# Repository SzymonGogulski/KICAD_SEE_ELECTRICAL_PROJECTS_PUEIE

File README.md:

**English version at the bottom.**
# Projektowanie Układów Elektrycznych i Elektronicznych
To repozytorium zawiera dokumentację oraz projekty wykonane w ramach przedmiotu Projektowanie Układów Elektrycznych i Elektronicznych na 7 semestrze kierunku Automatyka i Robotyka na Politechnice Poznańskiej. Autorami projektów są Marcin Gałąska i Szymon Gogulski.
### Główne cele projektów
1. <b> Opracowanie projektu układu elektrycznego sterującego mikroklimatem terrarium dla kameleona. </b>
    - Układ steruje parametrami mikroklimatu terrarium.
    - Automatyczna regulacja temperatury poprzez jedną dzienną oraz jedną nocną lampę grzewczą. 
    - Automatyczna regulacja oświetlenia poprzez świetlówkę UVB.
    - Automatyczna regulacja wilgotności poprzez zanurzony w zbiorniku wodnym fogger.
    - Pomiar temperatury i wilgotności powietrza poprzez czujniki z przetwornikami.
    - Informowanie o stanie mikroklimatu poprzez panel HMI.
2. <b> Opracowanie projektu układu elektronicznego oraz projektu płytki PCB dalmierza laserowego. </b>
    - Urządzenie wykonuje pomiar odległości czujnikiem laserowym i ultradźwiękowym.
    - Urządzenie jest zasilane z ogniwa LI-ION lub z baterii 9V.
    - Urządzenie posiada 6 przycisków.
    - Urządzenie posiada wyświetlacz LCD 4x20.
    - Urządzenie wykonuje pomiar naładowania akumulatora/ baterii.
    - Urządzenie obsługuje transmisję bluetooth.
***
# Dalmierz
- Projekt opiera się o dokumentację mikroprocesora RP2040.
- Projekt został wykonany w programi KiCad7.0.

### Schemat ideowy projektu

### Schemat elektronicznych

Schemat lepiej widoczny w jasnym motywie GitHub.

### Płytka PCB

### Płytka PCB 3D

### Zasilanie 
1. W celu zasilenia układu wykorzystaliśmy ogniwo li-ion 18650.
2. Układ składa się z dwóch przetwornic: BUCK-BOOST RT6150B-33GQW zapewniającej napięcie 3.3V oraz BOOST LM2775DSG zapewniającej napięcie 5V.
3. Przed wybraniem przetwornic przeprowadziliśmy rachunek poboru prądu przy założeniu najwyższego obciążenia.
4. W ramach monitorowania stanu naładowania ogniwa zastosowaliśmy moduł LC709203. Moduł ten umożliwia bieżące przekazywanie informacji o stanie ogniwa poprzez interface I2C do mikrokontrolera.
5. Wejścia układu zostały zabezpieczone diodami Schottkiego na wypadek odwrotnego zamontowania ogniwa w gnieździe.

### Czujniki
Czujniki odległości będą podłączane do układu poprzez konektory I2C

### Bluetooth
W ramach możliwości zapisu pomiarów na urządzeniu zewnętrznym dodaliśmy moduł komunikacji bluetooth.

### Macierz przycisków / Wyświetlacz I2C LCD
1. Jako interface użytkownika zastosowaliśmy macierz  sześciu przycisków oraz wyświetlacz I2C.
2. Na płytce zamontowaliśmy osobny konektory I2C umożliwiający podłączenie wyświetlacza.
3. W celu uniknięcia drgań styków lepszym rozwiązanie byłoby zastosowanie dodatkowych filtrów RC pomiędzy przyciskami oraz mikrokontrolerem.

### RP2040, pamięć Flash i oscylator
Sercem układu jest mikrokontroler RP2040, sugerowany schemat mikrokontrolera, pamięci flash i oscylatora kwarcowego został wykorzystany z ogólnodostępnej dokumentacji.
### Programowanie
Wejście USB micro B zostało dodane, aby umożliwić bieżący rozwój oprogramowania.

***

# Terarrium
- Projekt opiera się o sterownik PLC DC/DC/RELAY firmy Siemens serii S7-1200 model 6ES7212-1HE40-0XB0.
- Projekt został wykonany w programie SEE Electrical V8R4.

### Zasilanie
1. Głównym źródłem zasilania układu jest standardowa jednofazowa linia AC 230V 50Hz z przewodem uziemiającym.
2. Obwód zasilania zawiera wyłącznik nadprądowy MCN110E oraz wkładkę bezpiecznikową 1115282107T dla fazy, wraz z wyłącznikiem różnicowoprądowym CFI6-25/2/003 dla żyły fazy i odniesienia.
3. Rozgałęzienia linii głównej przechodzą przez styki stycznika iCT50-25-20-230, włączonego w obwód włącznika i wyłącznika głównego.
4. Podłączonym do głównej linii zasilania jest zasilacz AST-PWR-7524 firmy Astor, konwertujący otrzymywane 230 AC na 24 DC, służące do zasilania szeregu komponentów w układzie.

### Czujniki
Pomiar temperatury wykonywany jest poprzez trójprzewodowy czujnik Pt100 sparowany z przetwornikiem AR580. Pomiar wilgotności powietrza realizowany jest poprzez układ czujnika z przetwornikiem AR250. Oba czujniki przekazują swój sygnał wejściowy z zakresu 0...10V DC na wejścia analogowe sterownika PLC. Oba czujniki zasilane są z linii 24V DC.

### Elementy wykonawcze
Grzanie nocne wykonuje lampa grzewcza Exo Terra Ceramic Heat Emitter 50W PT2044, wkręcona w żaroodporny klosz PT2060. Grzanie nocne wykonuje lampa grzewcza Exo Terra Night Heat Lamp 25W PT2122, wkręcona w żaroodporny klosz PT2060. Oświetlenie terrarium zapewniane jest poprzez świetlówkę Exo Terra Reptile UVB Nano 9W PT2366, wkręconą w klosz PT2364. Elementem nawilżającym powietrze wewnątrz terrarium jest membranowy fogger Exo Terra Fogger Ultrasonic Fog Generator PT2080. Elementy te zasilane są z sieci 230 AC, jednak w swoich obwodach posiadają styki styczników pomocniczych CA3SK11BD, których cewki podłączone są do wyjść cyfrowych sterownika PLC, celem kontroli zasilania każdego z elementów wykonawczych.

### Wizualizacja stanu mikroklimatu
Elementem informującym użytkownika o parametrach mikroklimatu terrarium jest panel HMI Simatic KTP400 6AV2123-2DB03-0AX0 firmy Siemens, połączony ze sterownikiem PLC poprzez złącze Ethernet.

### Szafa rozdzielcza

***

# Design of Electrical and Electronic Systems
This repository contains documentation and projects made as part of the course Design of Electrical and Electronic Systems in the 7th semester of the Automation and Robotics major at the Poznań University of Technology. The authors of the projects are Marcin Gałąska and Szymon Gogulski.
### Main project goals
1. <b> Development of an electrical system controlling the microclimate of a chameleon terrarium. </b>
    - The system controls the parameters of the terrarium microclimate.
    - Automatic temperature control using one daytime and one nighttime heating lamp.
    - Automatic lighting control using a UVB fluorescent lamp.
    - Automatic humidity control using a fogger immersed in the water tank.
    - Measurement of air temperature and humidity using sensors with transducers.
    - Information about the microclimate status using the HMI panel.
2. <b> Development of an electronic circuit and a PCB design for a laser rangefinder. </b>
    - The device measures distance with a laser and ultrasonic sensor.
    - The device is powered by a LI-ION cell or a 9V battery.
    - The device has 6 buttons.
    - The device has a 4x20 LCD display.
    - The device measures the battery charge.
    - The device supports Bluetooth transmission.
***
# Rangefinder
- The project is based on the RP2040 microprocessor documentation.
- The project was made in KiCad7.0.

### Project flowchart

### Electronic diagram

Diagram more visible in GitHub's light theme.

### PCB board

### PCB board 3D view

### Power supply
1. To power the system, we used a 18650 Li-ion cell.
2. The system consists of two converters: BUCK-BOOST RT6150B-33GQW providing a voltage of 3.3V and BOOST LM2775DSG providing a voltage of 5V.
3. Before selecting the converters, we calculated the current consumption assuming the highest load.
4. TO monitor the cell charge status, we used the LC709203 module. This module allows the transmission of information about the cell status via the I2C interface to the microcontroller.
5. The inputs of the system were protected with Schottky diodes in case the cell is mounted in the socket the other way around.

### Sensors
Distance sensors will be connected to the system via I2C connectors

### Bluetooth
In order to enable the recording of measurements on an external device, we have added a Bluetooth communication module.

### Button matrix / I2C LCD display
1. We have used a matrix of six buttons and an I2C display as the user interface.

2. We have mounted separate I2C connectors on the board to connect the display.

3. In order to avoid contact vibrations, a better solution would be to use additional RC filters between the buttons and the microcontroller.

### RP2040, Flash memory and oscillator
The heart of the system is the RP2040 microcontroller, the suggested diagram of the microcontroller, flash memory and quartz oscillator was used from publicly available documentation.

### Programming
The USB micro B inputs were left to enable ongoing software development.

***

# Terarrium
- The project is based on the Siemens S7-1200 series PLC DC/DC/RELAY model 6ES7212-1HE40-0XB0.
- The project was made in the SEE Electrical V8R4 program.

### Power supply
1. The main power supply for the system is a standard single-phase AC 230V 50Hz line with a ground wire.

2. The power supply circuit includes an MCN110E circuit breaker and a 1115282107T fuse insert for the phase, along with a CFI6-25/2/003 differential circuit breaker for the phase and reference wires.

3. The main line branches pass through the contacts of the iCT50-25-20-230 contactor, included in the main switch and switch circuit.
4. Connected to the main power line is the Astor AST-PWR-7524 power supply, converting the received 230 AC to 24 DC, used to power a number of components in the system.

### Sensors
Temperature measurement is performed by a three-wire Pt100 sensor paired with an AR580 transducer. Air humidity measurement is performed by a sensor system with an AR250 transducer. Both sensors transmit their input signal from the 0...10V DC range to the analog inputs of the PLC controller. Both sensors are powered from the 24V DC line.

### Actuators
Night heating is performed by the Exo Terra Ceramic Heat Emitter 50W PT2044 heating lamp, screwed into a heat-resistant PT2060 lampshade. Night heating is performed by the Exo Terra Night Heat Lamp 25W PT2122 heating lamp, screwed into a heat-resistant PT2060 lampshade. Terrarium lighting is provided by an Exo Terra Reptile UVB Nano 9W PT2366 fluorescent lamp, screwed into a PT2364 lampshade. The element that humidifies the air inside the terrarium is the Exo Terra Fogger Ultrasonic Fog Generator PT2080 membrane fogger. These elements are powered from the 230 AC network, but in their circuits they have contacts of auxiliary contactors CA3SK11BD, the coils of which are connected to the digital outputs of the PLC controller, in order to control the power supply of each of the executive elements.

### Visualization of the microclimate state
The element informing the user about the parameters of the terrarium microclimate is the HMI panel Simatic KTP400 6AV2123-2DB03-0AX0 by Siemens, connected to the PLC controller via an Ethernet port.

### Switchboard

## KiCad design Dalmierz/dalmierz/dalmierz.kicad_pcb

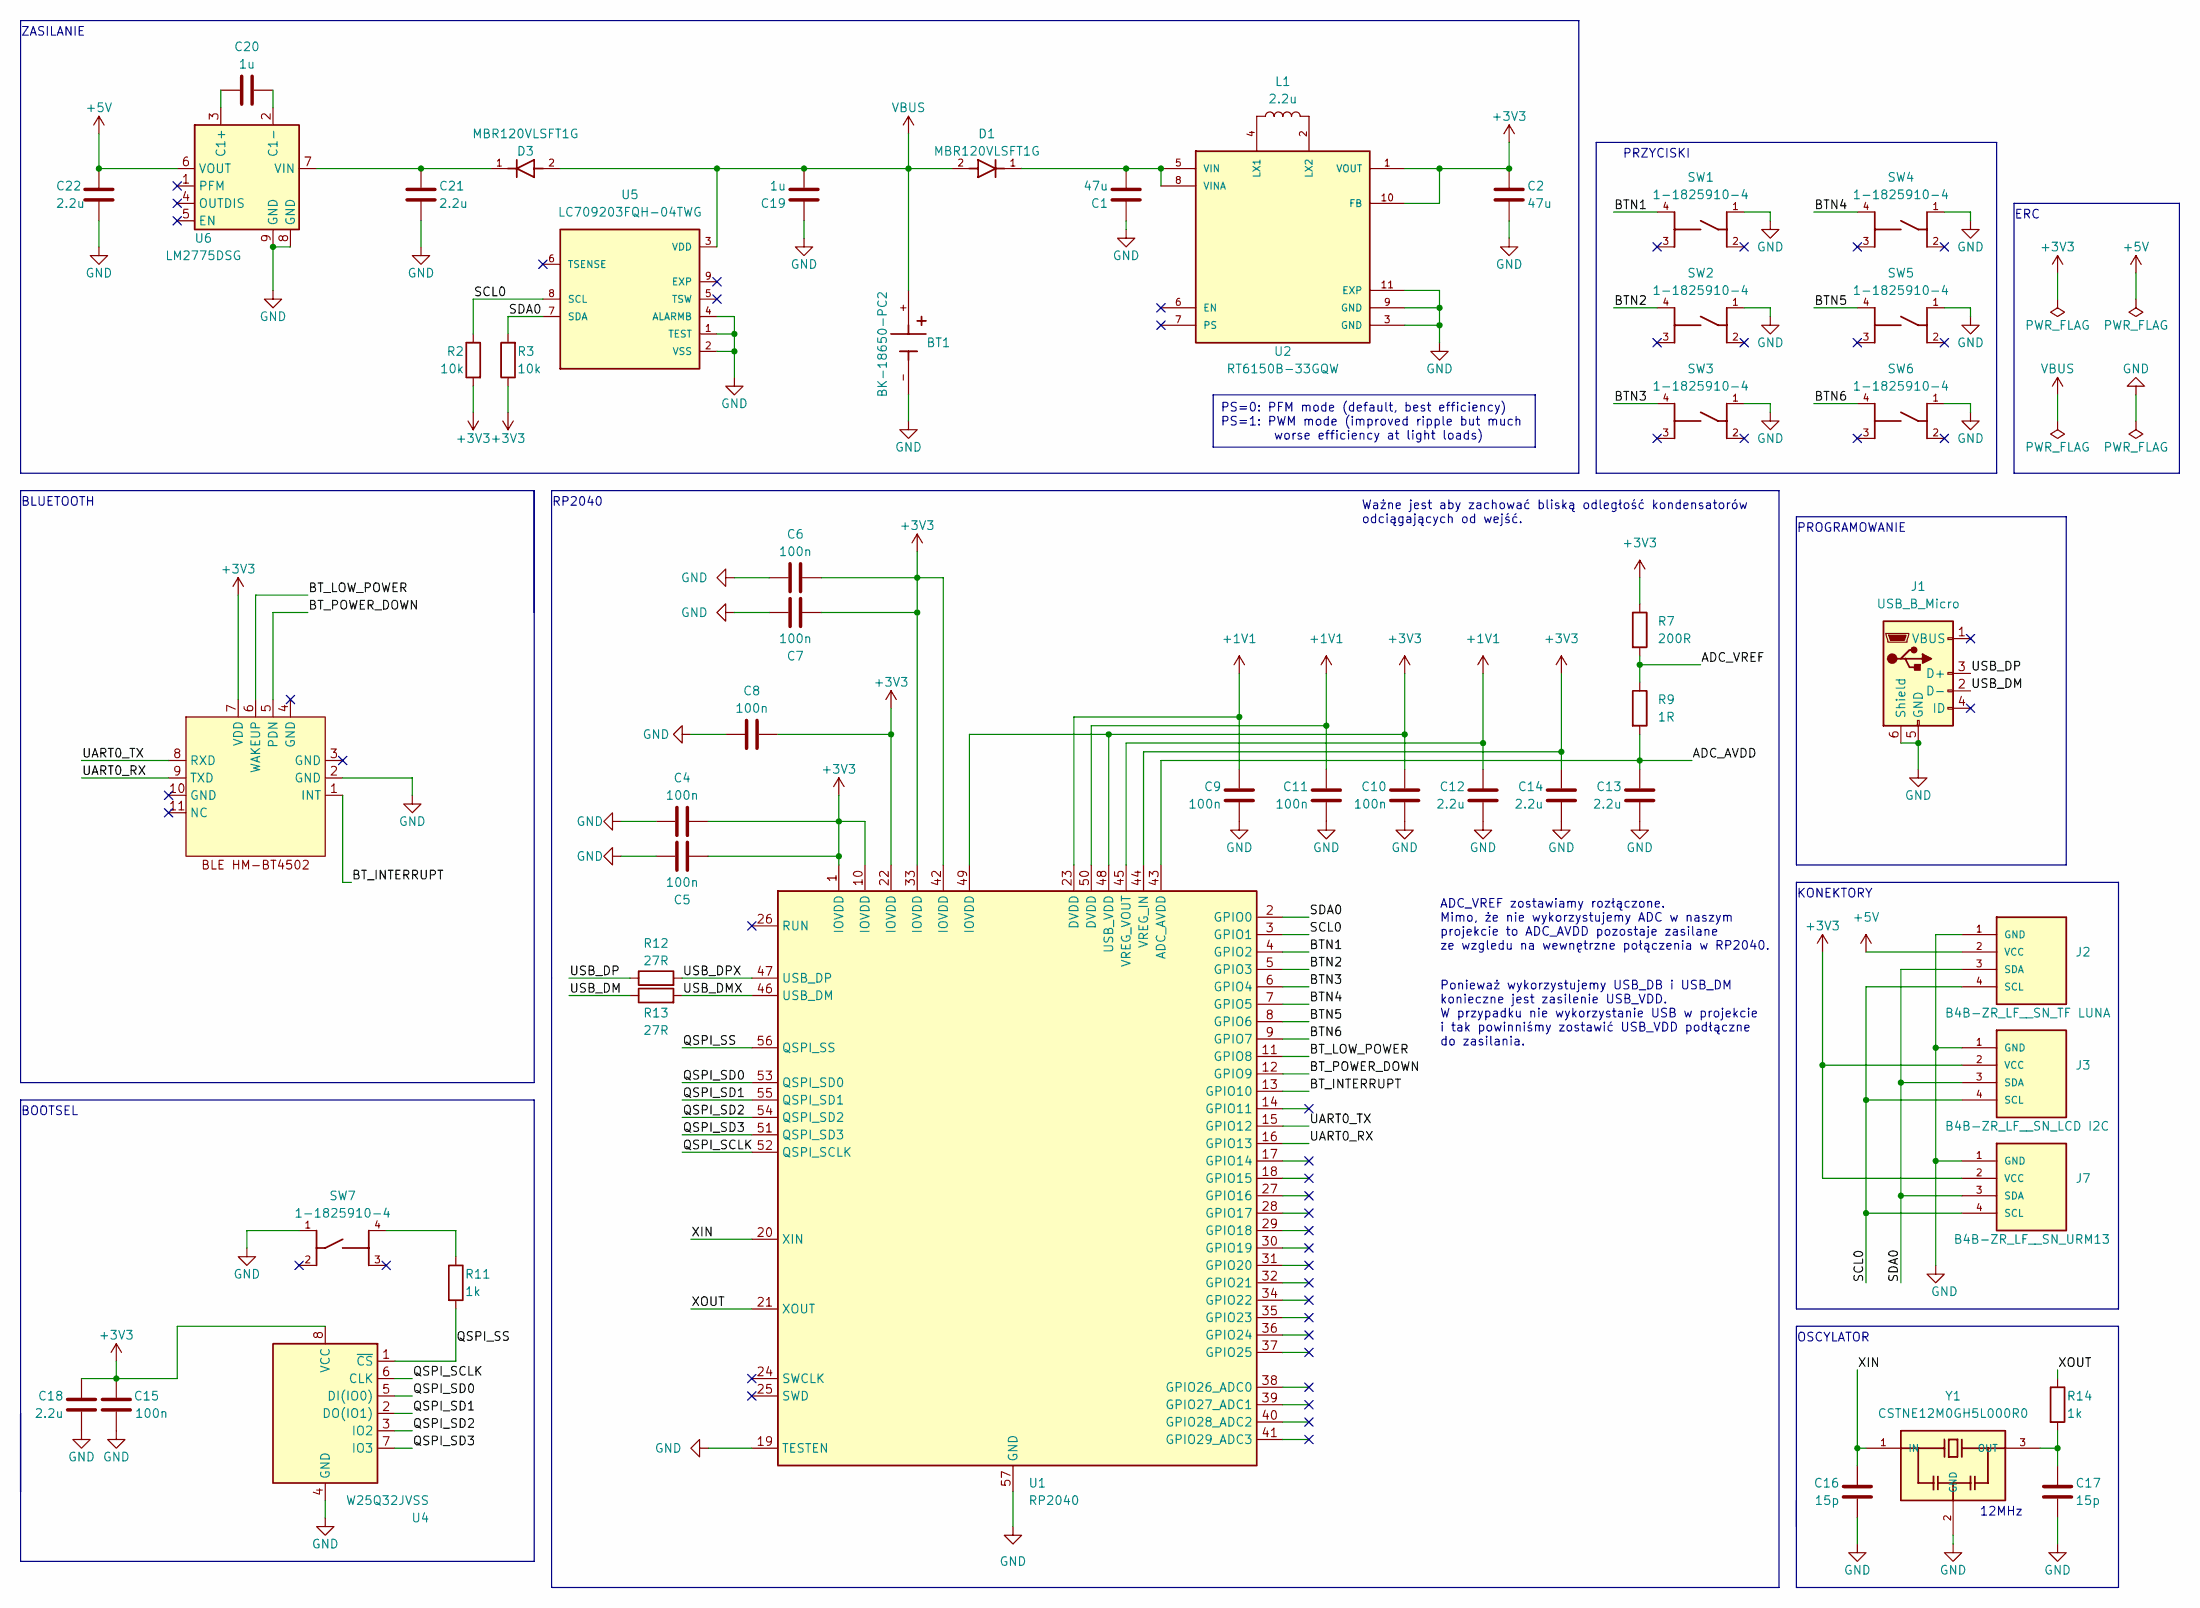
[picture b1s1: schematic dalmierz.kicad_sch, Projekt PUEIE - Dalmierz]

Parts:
B1: BLE_HM-BT5402
BT1: BK-18650-PC2; BAT_BK-18650-PC2; PARTREV F
C1, C2: 47u; C_0603_1608Metric
C4, C5, C6, C7, C8, C9, C10, C11, C15: 100n; C_0603_1608Metric
C12, C13, C14, C18, C21, C22: 2.2u; C_0603_1608Metric
C16, C17: 15p; C_0603_1608Metric
C19, C20: 1u; C_0603_1608Metric
D1, D3: MBR120VLSFT1G; DIOM3616X98N; PARTREV 5/10/2013
J1: USB_B_Micro; USB_Micro-B_Amphenol_10103594-0001LF_Horizontal
J2: B4B-ZR_LF__SN_TF LUNA; JST_B4B-ZR_LF__SN_
J3: B4B-ZR_LF__SN_LCD I2C; JST_B4B-ZR_LF__SN_
J7: B4B-ZR_LF__SN_URM13; JST_B4B-ZR_LF__SN_
L1: 2.2u; L_0603_1608Metric
R2, R3: 10k; R_0603_1608Metric
R7: 200R; R_0603_1608Metric
R9: 1R; R_0603_1608Metric
R11, R14: 1k; R_0603_1608Metric
R12, R13: 27R; R_0603_1608Metric
SW1, SW2, SW3, SW4, SW5, SW6, SW7: 1-1825910-4; TE_1-1825910-4; PARTREV C10
U1: RP2040; QFN-56-1EP_7x7mm_P0.4mm_EP3.2x3.2mm
U2: RT6150B-33GQW; SON50P250X250X80-11N; PARTREV July 2018
U4: W25Q32JVSS; SOIC-8_5.23x5.23mm_P1.27mm
U5: LC709203FQH-04TWG; DFN300X400X80-8N
U6: LM2775DSG; WSON-8-1EP_2x2mm_P0.5mm_EP0.9x1.6mm
Y1: CSTNE12M0GH5L000R0; OSC_CSTNE12M0GH5L000R0; PARTREV JGC42-8858A

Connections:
+1V1: C9.1, C11.1, C12.1, U1.23 (DVDD), U1.45 (VREG_VOUT), U1.50 (DVDD)
+3V3: B1.7 (VDD), C2.1, C4.2, C5.2, C6.2, C7.2, C8.2, C10.1, C14.1, C15.1, C18.1, J3.2 (VCC), J7.2 (VCC), R2.2, R3.1, R7.1, U1.1 (IOVDD), U1.10 (IOVDD), U1.22 (IOVDD), U1.33 (IOVDD), U1.42 (IOVDD), U1.44 (VREG_IN), U1.48 (USB_VDD), U1.49 (IOVDD), U2.1 (VOUT), U2.10 (FB), U4.8 (VCC); also elsewhere on the board
+5V: C22.1, J2.2 (VCC), U6.6 (VOUT)
/ADC_AVDD: C13.1, R9.2, U1.43 (ADC_AVDD)
/ADC_VREF: R7.2, R9.1
/BTN1: SW1.4, U1.4 (GPIO2)
/BTN2: SW2.4, U1.5 (GPIO3)
/BTN3: SW3.4, U1.6 (GPIO4)
/BTN4: SW4.4, U1.7 (GPIO5)
/BTN5: SW5.4, U1.8 (GPIO6)
/BTN6: SW6.4, U1.9 (GPIO7)
/BT_INTERRUPT: B1.1 (INT), U1.13 (GPIO10)
/BT_LOW_POWER: B1.6 (WAKEUP), U1.11 (GPIO8)
/BT_POWER_DOWN: B1.5 (PDN), U1.12 (GPIO9)
/QSPI_SCLK: U1.52 (QSPI_SCLK), U4.6 (CLK)
/QSPI_SD0: U1.53 (QSPI_SD0), U4.5 (DI(IO0))
/QSPI_SD1: U1.55 (QSPI_SD1), U4.2 (DO(IO1))
/QSPI_SD2: U1.54 (QSPI_SD2), U4.3 (IO2)
/QSPI_SD3: U1.51 (QSPI_SD3), U4.7 (IO3)
/QSPI_SS: R11.2, U1.56 (QSPI_SS), U4.1 (~CS)
/SCL0: J2.4 (SCL), J3.4 (SCL), J7.4 (SCL), R2.1, U1.3 (GPIO1), U5.8 (SCL)
/SDA0: J2.3 (SDA), J3.3 (SDA), J7.3 (SDA), R3.2, U1.2 (GPIO0), U5.7 (SDA)
/UART0_RX: B1.9 (TXD), U1.16 (GPIO13)
/UART0_TX: B1.8 (RXD), U1.15 (GPIO12)
/USB_DM: J1.2 (D-), R13.1
/USB_DMX: R13.2, U1.46 (USB_DM)
/USB_DP: J1.3 (D+), R12.1
/USB_DPX: R12.2, U1.47 (USB_DP)
/XIN: C16.1, U1.20 (XIN), Y1.1 (IN)
/XOUT: R14.1, U1.21 (XOUT)
GND: B1.2 (GND), B1.3 (GND), B1.4 (GND), B1.10 (GND), B1.11 (NC), BT1.-, C1.1, C2.2, C4.1, C5.1, C6.1, C7.1, C8.1, C9.2, C10.2, C11.2, C12.2, C13.2, C14.2, C15.2, C16.2, C17.2, C18.2, C19.1, C21.1, C22.2, J1.5 (GND), J1.6 (Shield), J2.1 (GND), J3.1 (GND), J7.1 (GND), SW1.1, SW2.1, SW3.1, SW4.1, SW5.1, SW6.1, SW7.1, U1.19 (TESTEN), U1.57 (GND), U2.3 (GND), U2.9 (GND), U2.11 (EXP), U4.4 (GND), U5.1 (TEST), U5.2 (VSS), U5.4 (ALARMB), U6.8 (GND), U6.9 (GND), Y1.2 (GND); also elsewhere on the board
unnamed: R11.1, SW7.4
unnamed: L1.1, U2.4 (LX1)
unnamed: L1.2, U2.2 (LX2)
unnamed: C1.2, D1.1, U2.5 (VIN), U2.8 (VINA)
unnamed: C20.2, U6.3 (C1+)
unnamed: C20.1, U6.2 (C1-)
unnamed: C21.2, D3.1, U6.7 (VIN)
unnamed: C17.1, R14.2, Y1.3 (OUT)
VBUS: BT1.+, C19.2, D1.2, D3.2, U5.3 (VDD)

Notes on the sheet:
PS=0: PFM mode (default, best efficiency) PS=1: PWM mode (improved ripple but much worse efficiency at light loads)
OSCYLATOR
PROGRAMOWANIE
BLUETOOTH
PRZYCISKI
ADC_VREF zostawiamy rozłączone. Mimo, że nie wykorzystujemy ADC w naszym projekcie to ADC_AVDD pozostaje zasilane ze wzgledu na wewnętrzne połączenia w RP2040.
ERC
Ponieważ wykorzystujemy USB_DB i USB_DM konieczne jest zasilenie USB_VDD. W przypadku nie wykorzystanie USB w projekcie i tak powinniśmy zostawić USB_VDD podłączne do zasilania.
KONEKTORY
RP2040
12MHz
ZASILANIE
Ważne jest aby zachować bliską odległość kondensatorów odciągających od wejść.
BOOTSEL

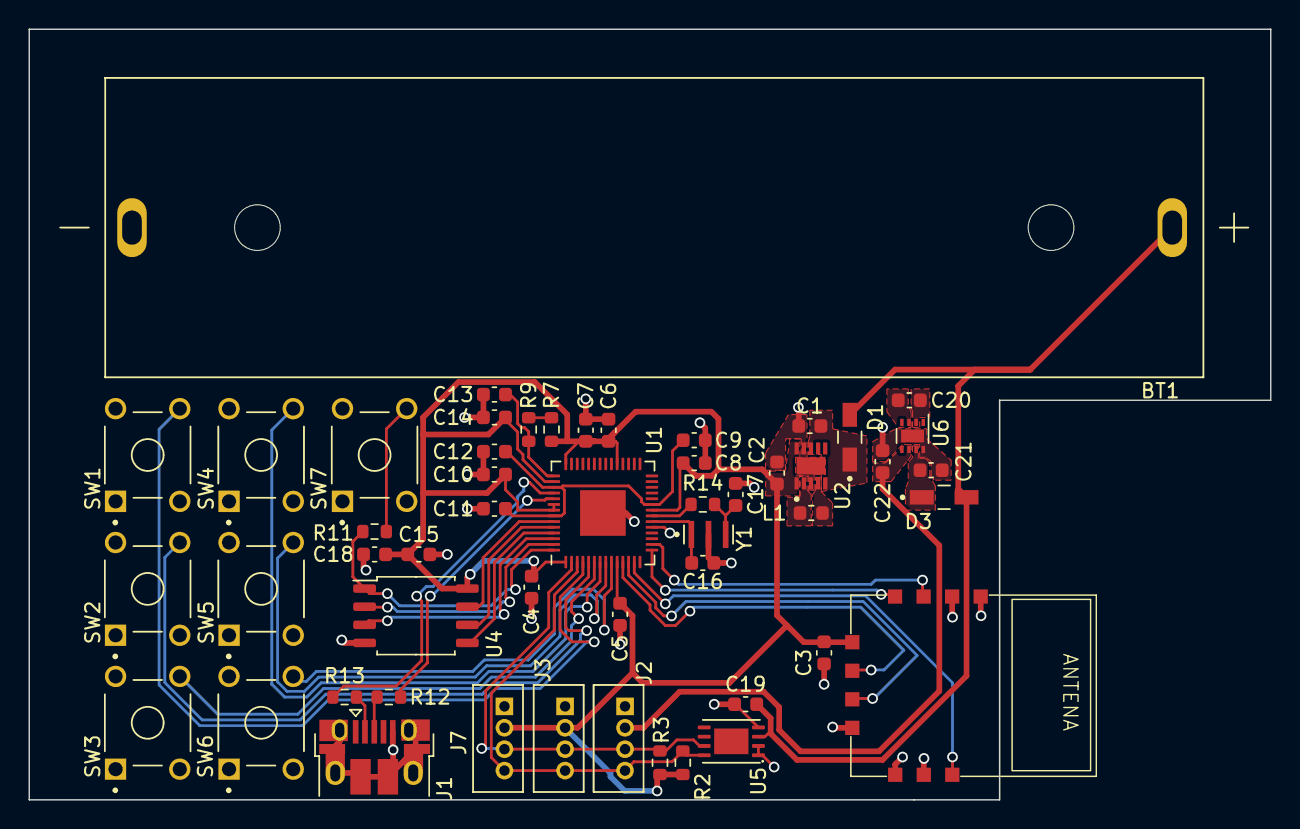
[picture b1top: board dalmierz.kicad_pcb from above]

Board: 2 copper layers, 87.0 x 54.0 mm, 52 parts (0 on the bottom side), 40 nets.

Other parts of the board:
C3: 100n; C_0603_1608Metric

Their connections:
+3V3: C3.2; also elsewhere on the board
GND: C3.1; also elsewhere on the board

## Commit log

2024-10-27 MAIN: Initial commit
2024-10-27 MAIN: corrected empty directories.
2024-10-30 MAIN: Poprawka schematu ideowego.
2024-11-01 MAIN: przerysowuje RPi pico do KiCad
2024-11-02 MAIN: work in progress.
2024-11-03 MAIN: Resolved issues: missing IOVDD, DVDD pins. Updated RP2040.
2024-11-15 Main: dodalem odpowiedzi na pytania.
2024-11-16 MAIN: dalmierz work in progress.
2024-11-16 Add device list and first iteration of electrical diagram
2024-11-16 MAIN: dalmierz.sch work in progress.
2024-11-17 MAIN: dalmierz dodaj BLUETOOTH.
2024-11-18 MAIN: Bluetooth work in progress.
2024-11-18 MAIN: pierwsza wersja dalmierz.sch.
2024-11-18 Add humidifier, minor corrections
2024-11-19 MAIN: 1 wersja dalmierz sch.
2024-11-19 MAIN: poprawilem wersje 1 sch.
2024-11-20 MAIN: footprinty work in progress.
2024-11-21 MAIN: PCB, rozmieszczenie komponentow.
2024-11-22 MAIN: footprinty, rozmieszczenie na PCB work in progress
2024-11-22 MAIN: PCB traces in progress.
2024-11-23 MAIN: rozwiazanie problemow PCB
2024-11-23 MAIN: Koniec tworzenia PBC.
2024-11-24 MAIN: Popraw błędów w PCB. Rozlanie masy itd.
2024-12-07 (Hopefully) finished Terrarium
2024-12-07 Uploaded correct Terrarium.docx
2024-12-11 dalmierz koniec
2024-12-11 MAIN: dalmierz dokumentacja
2024-12-19 MAIN: ostatnia zmiana
2024-12-19 MAIN: README dalmierz
2024-12-20 Upload Terrarium README images
2024-12-20 Update README with Terrarium info
2024-12-26 poprawka schematu w README.md
